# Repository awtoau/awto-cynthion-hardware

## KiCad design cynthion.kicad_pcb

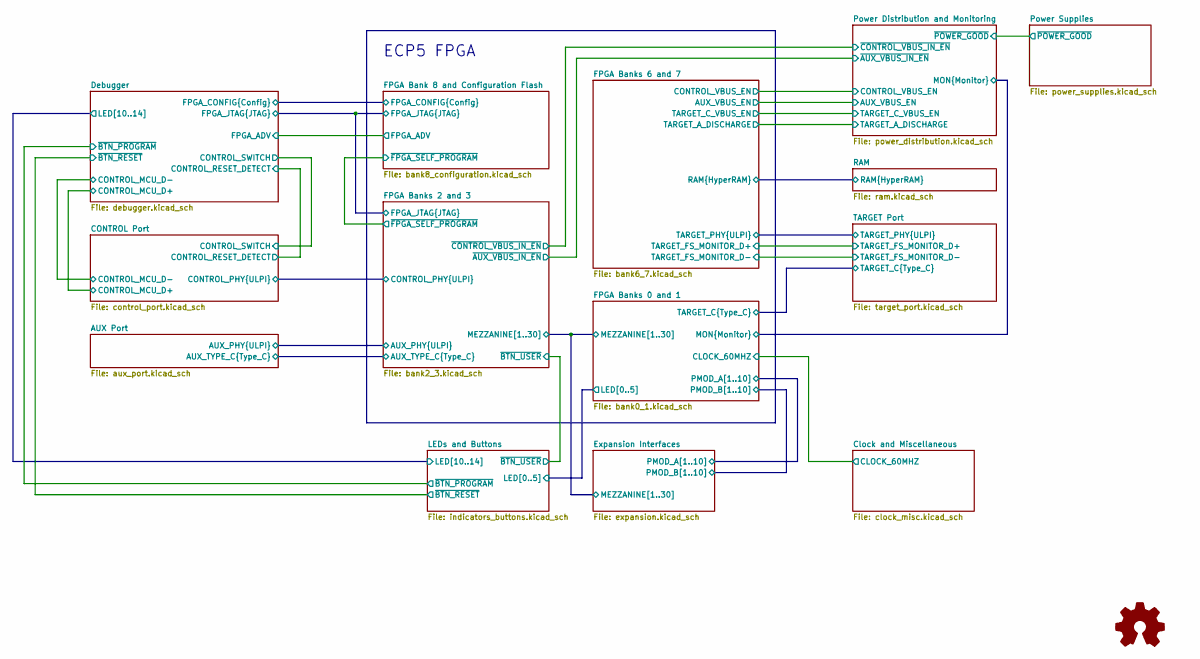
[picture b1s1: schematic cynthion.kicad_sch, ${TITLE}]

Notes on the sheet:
ECP5 FPGA

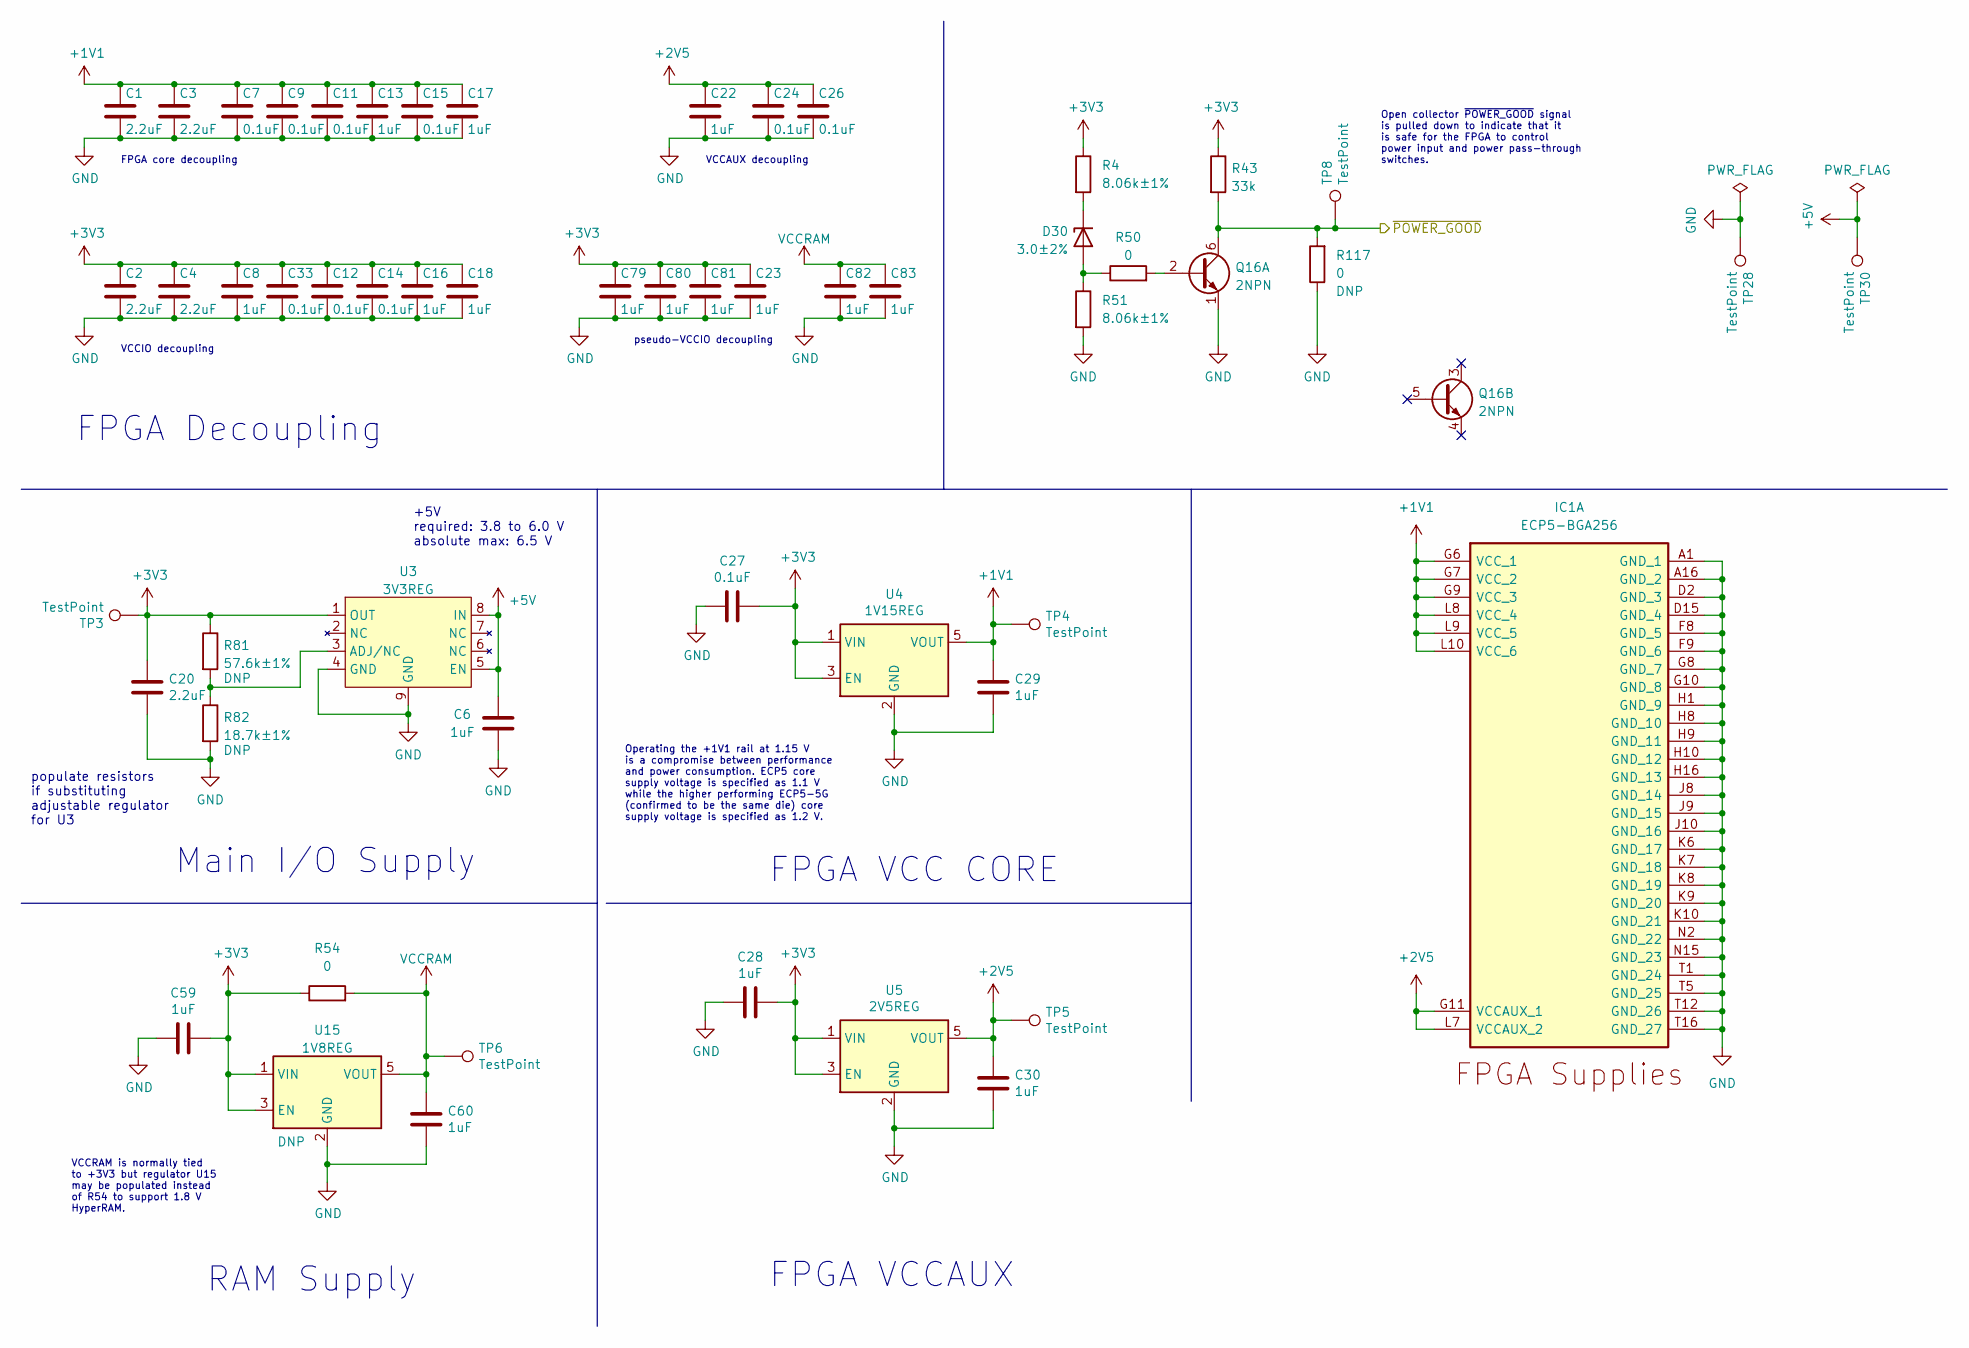
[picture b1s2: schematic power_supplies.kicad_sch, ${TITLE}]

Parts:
C1, C2, C3, C4, C20: 2.2uF; C_0603_1608Metric; Part Number CL10A225KP8NNNC
C6, C8, C13, C16, C17, C18, C22, C23, C28, C29, C30, C59, C60, C79, C80, C81, C82, C83: 1uF; C_0402_1005Metric; Part Number CL05A105MQ5NNNC
C7, C9, C11, C12, C14, C15, C24, C26, C27, C33: 0.1uF; C_0402_1005Metric; Part Number CL05A104KA5NNNC
D30: 3.0±2%; DFN1006-2; Part Number BZX884-B3V0,315
IC1: ECP5-BGA256; lattice_cabga256; Part Number LFE5U-12F-6BG256C
Q16: 2NPN; SOT-363_SC-70-6; Part Number BC847BS
R4, R51: 8.06k±1%; R_0402_1005Metric; Part Number ERJ-2RKF8061X
R43: 33k; R_0402_1005Metric; Part Number ERJ-2GEJ333X
R50, R54, R117: 0; R_0402_1005Metric; Part Number RC0402FR-070RL
R81: 57.6k±1%; R_0402_1005Metric; Part Number RC0402FR-0757K6L
R82: 18.7k±1%; R_0402_1005Metric; Part Number ERJ-2RKF1872X
TP3, TP4, TP5, TP6, TP8, TP28, TP30: TestPoint; TestPoint_Pad_D1.0mm
U3: 3V3REG; DFN-8-1EP_3x3mm_P0.65mm_EP1.55x2.4mm; Part Number AP7361EA-33FGE-7
U4: 1V15REG; SOT-23-5; Part Number TCR2EF115,LM(CT
U5: 2V5REG; SOT-23-5; Part Number MIC5504-2.5YM5-TR
U15: 1V8REG; SOT-23-5; Part Number MIC5504-1.8YM5-TR

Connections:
+1V1: C1.1, C3.1, C7.1, C9.1, C11.1, C13.1, C15.1, C17.1, C29.1, IC1.G6 (VCC_1), IC1.G7 (VCC_2), IC1.G9 (VCC_3), IC1.L8 (VCC_4), IC1.L9 (VCC_5), IC1.L10 (VCC_6), TP4.1 (1_1), U4.5 (VOUT)
+2V5: C22.1, C24.1, C26.1, C30.1, IC1.G11 (VCCAUX_1), IC1.L7 (VCCAUX_2), TP5.1 (1_1), U5.5 (VOUT)
+3V3: C2.1, C4.1, C8.1, C12.1, C14.1, C16.1, C18.1, C20.1, C23.1, C27.1, C28.1, C33.1, C59.1, C79.1, C80.1, C81.1, R4.1, R43.1, R54.1, R81.1, TP3.1 (1_1), U3.1 (OUT), U4.1 (VIN), U4.3 (EN), U5.1 (VIN), U5.3 (EN), U15.1 (VIN), U15.3 (EN); also elsewhere on the board
+5V: C6.1, TP30.1 (1_1), U3.5 (EN), U3.8 (IN); also elsewhere on the board
/Power Distribution and Monitoring/~POWER_GOOD: Q16.6 (C1), R43.2, R117.2, TP8.1 (1_1); also elsewhere on the board
GND: C1.2, C2.2, C3.2, C4.2, C6.2, C7.2, C8.2, C9.2, C11.2, C12.2, C13.2, C14.2, C15.2, C16.2, C17.2, C18.2, C20.2, C22.2, C23.2, C24.2, C26.2, C27.2, C28.2, C29.2, C30.2, C33.2, C59.2, C60.2, C79.2, C80.2, C81.2, C82.2, C83.2, IC1.A1 (GND_1), IC1.A16 (GND_2), IC1.D2 (GND_3), IC1.D15 (GND_4), IC1.F8 (GND_5), IC1.F9 (GND_6), IC1.G8 (GND_7), IC1.G10 (GND_8), IC1.H1 (GND_9), IC1.H8 (GND_10), IC1.H9 (GND_11), IC1.H10 (GND_12), IC1.H16 (GND_13), IC1.J8 (GND_14), IC1.J9 (GND_15), IC1.J10 (GND_16), IC1.K6 (GND_17), IC1.K7 (GND_18), IC1.K8 (GND_19), IC1.K9 (GND_20), IC1.K10 (GND_21), IC1.N2 (GND_22), IC1.N15 (GND_23), IC1.T1 (GND_24), IC1.T5 (GND_25), IC1.T12 (GND_26), IC1.T16 (GND_27), Q16.1 (E1), R51.2, R82.2, R117.1, TP28.1 (1_1), U3.4 (GND), U3.9 (GND), U4.2 (GND), U5.2 (GND), U15.2 (GND); also elsewhere on the board
unnamed: D30.2 (A), R50.1, R51.1
unnamed: D30.1 (K), R4.2
unnamed: Q16.2 (B1), R50.2
unnamed: R81.2, R82.1, U3.3 (ADJ/NC)
VCCRAM: C60.1, C82.1, C83.1, R54.2, TP6.1 (1_1), U15.5 (VOUT); also elsewhere on the board

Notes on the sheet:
VCCIO decoupling
FPGA VCC CORE
FPGA Decoupling
FPGA core decoupling
+5V required: 3.8 to 6.0 V absolute max: 6.5 V
VCCRAM is normally tied to +3V3 but regulator U15 may be populated instead of R54 to support 1.8 V HyperRAM.
Open collector ~{POWER_GOOD} signal is pulled down to indicate that it is safe for the FPGA to control power input and power pass-through switches.
VCCAUX decoupling
FPGA VCCAUX
Main I/O Supply
populate resistors if substituting adjustable regulator for U3
RAM Supply
Operating the +1V1 rail at 1.15 V is a compromise between performance and power consumption. ECP5 core supply voltage is specified as 1.1 V while the higher performing ECP5-5G (confirmed to be the same die) core supply voltage is specified as 1.2 V.
pseudo-VCCIO decoupling

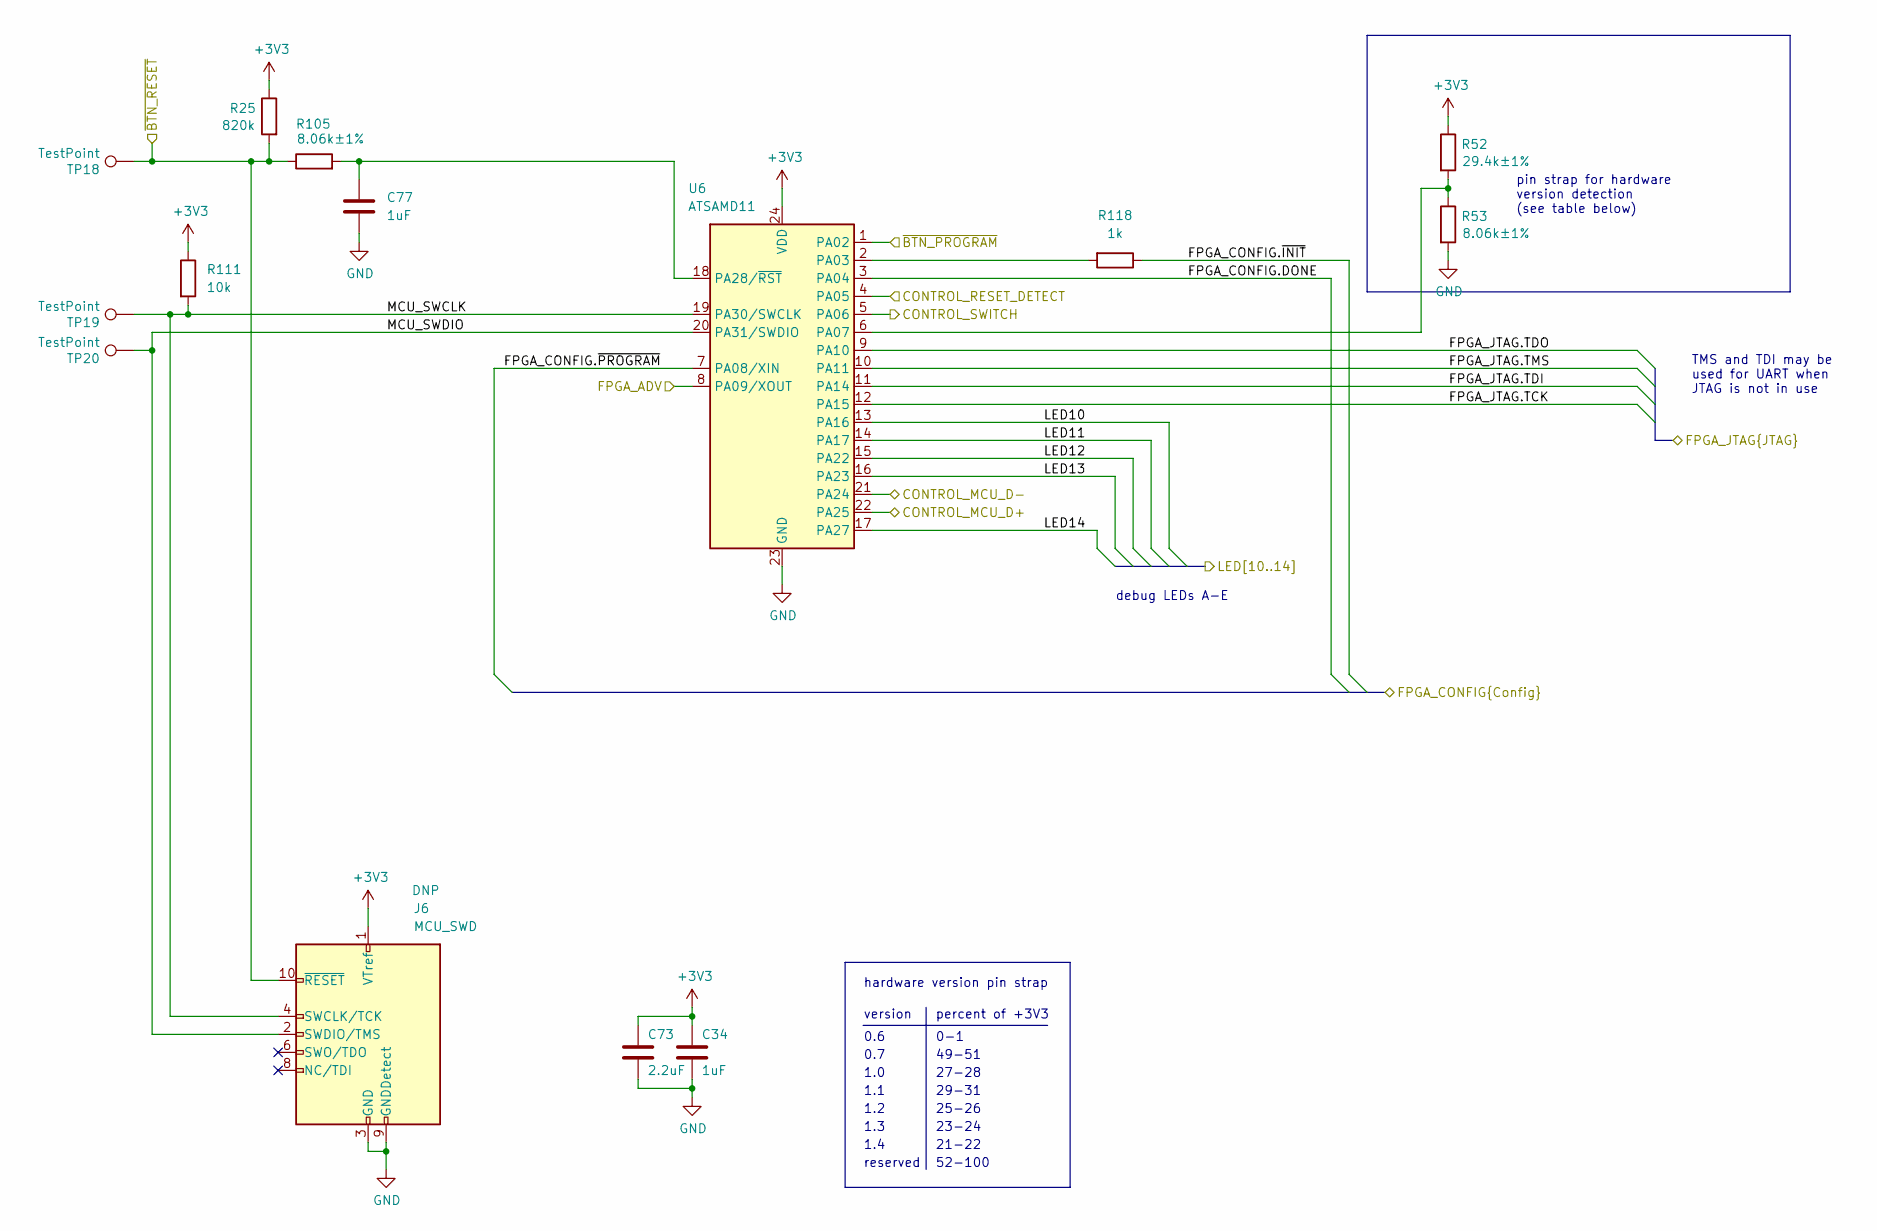
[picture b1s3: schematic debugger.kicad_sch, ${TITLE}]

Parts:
C34, C77: 1uF; C_0402_1005Metric; Part Number CL05A105MQ5NNNC
C73: 2.2uF; C_0603_1608Metric; Part Number CL10A225KP8NNNC
J6: MCU_SWD; SWD_CONNECTOR_LARGE_BOX; Part Number FTSH-105-01-F-D-K
R25: 820k; R_0402_1005Metric; Part Number RC0402JR-07820KL
R52: 29.4k±1%; R_0402_1005Metric; Part Number RC0402FR-0729K4L
R53, R105: 8.06k±1%; R_0402_1005Metric; Part Number ERJ-2RKF8061X
R111: 10k; R_0402_1005Metric; Part Number RC0402JR-0710KL
R118: 1k; R_0402_1005Metric; Part Number RC0402JR-071KL
TP18, TP19, TP20: TestPoint; TestPoint_Pad_D1.0mm
U6: ATSAMD11; QFN-24-1EP_4x4mm_P0.5mm_EP2.6x2.6mm; Part Number ATSAMD11D14A-MUT

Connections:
+3V3: C34.1, C73.1, J6.1 (VTref), R25.1, R52.1, R111.1, U6.24 (VDD); also elsewhere on the board
/CONTROL Port/CONTROL_MCU_D+: U6.22 (PA25); also elsewhere on the board
/CONTROL Port/CONTROL_MCU_D-: U6.21 (PA24); also elsewhere on the board
/CONTROL Port/CONTROL_RESET_DETECT: U6.4 (PA05); also elsewhere on the board
/CONTROL Port/CONTROL_SWITCH: U6.5 (PA06); also elsewhere on the board
/Debugger/FPGA_ADV: U6.8 (PA09/XOUT); also elsewhere on the board
/Debugger/FPGA_CONFIG.DONE: U6.3 (PA04); also elsewhere on the board
/Debugger/FPGA_CONFIG.~INIT: R118.1; also elsewhere on the board
/Debugger/FPGA_CONFIG.~PROGRAM: U6.7 (PA08/XIN); also elsewhere on the board
/Debugger/FPGA_JTAG.TCK: U6.12 (PA15); also elsewhere on the board
/Debugger/FPGA_JTAG.TDI: U6.11 (PA14); also elsewhere on the board
/Debugger/FPGA_JTAG.TDO: U6.9 (PA10); also elsewhere on the board
/Debugger/FPGA_JTAG.TMS: U6.10 (PA11); also elsewhere on the board
/Debugger/LED10: U6.13 (PA16); also elsewhere on the board
/Debugger/LED11: U6.14 (PA17); also elsewhere on the board
/Debugger/LED12: U6.15 (PA22); also elsewhere on the board
/Debugger/LED13: U6.16 (PA23); also elsewhere on the board
/Debugger/LED14: U6.17 (PA27); also elsewhere on the board
/Debugger/MCU_SWCLK: J6.4 (SWCLK/TCK), R111.2, TP19.1 (1_1), U6.19 (PA30/SWCLK)
/Debugger/MCU_SWDIO: J6.2 (SWDIO/TMS), TP20.1 (1_1), U6.20 (PA31/SWDIO)
/Debugger/~BTN_PROGRAM: U6.1 (PA02); also elsewhere on the board
/Debugger/~BTN_RESET: J6.10 (~RESET), R25.2, R105.1, TP18.1 (1_1); also elsewhere on the board
GND: C34.2, C73.2, C77.2, J6.3 (GND), J6.5 (GND), J6.9 (GNDDetect), R53.2, U6.23 (GND); also elsewhere on the board
unnamed: R118.2, U6.2 (PA03)
unnamed: R52.2, R53.1, U6.6 (PA07)
unnamed: C77.1, R105.2, U6.18 (PA28/~RST)

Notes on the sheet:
1.4
debug LEDs A-E
reserved
27-28
52-100
version
25-26
percent of +3V3
TMS and TDI may be used for UART when JTAG is not in use
29-31
0.6
0-1
1.0
23-24
pin strap for hardware version detection (see table below)
49-51
1.2
0.7
1.3
21-22
1.1
hardware version pin strap

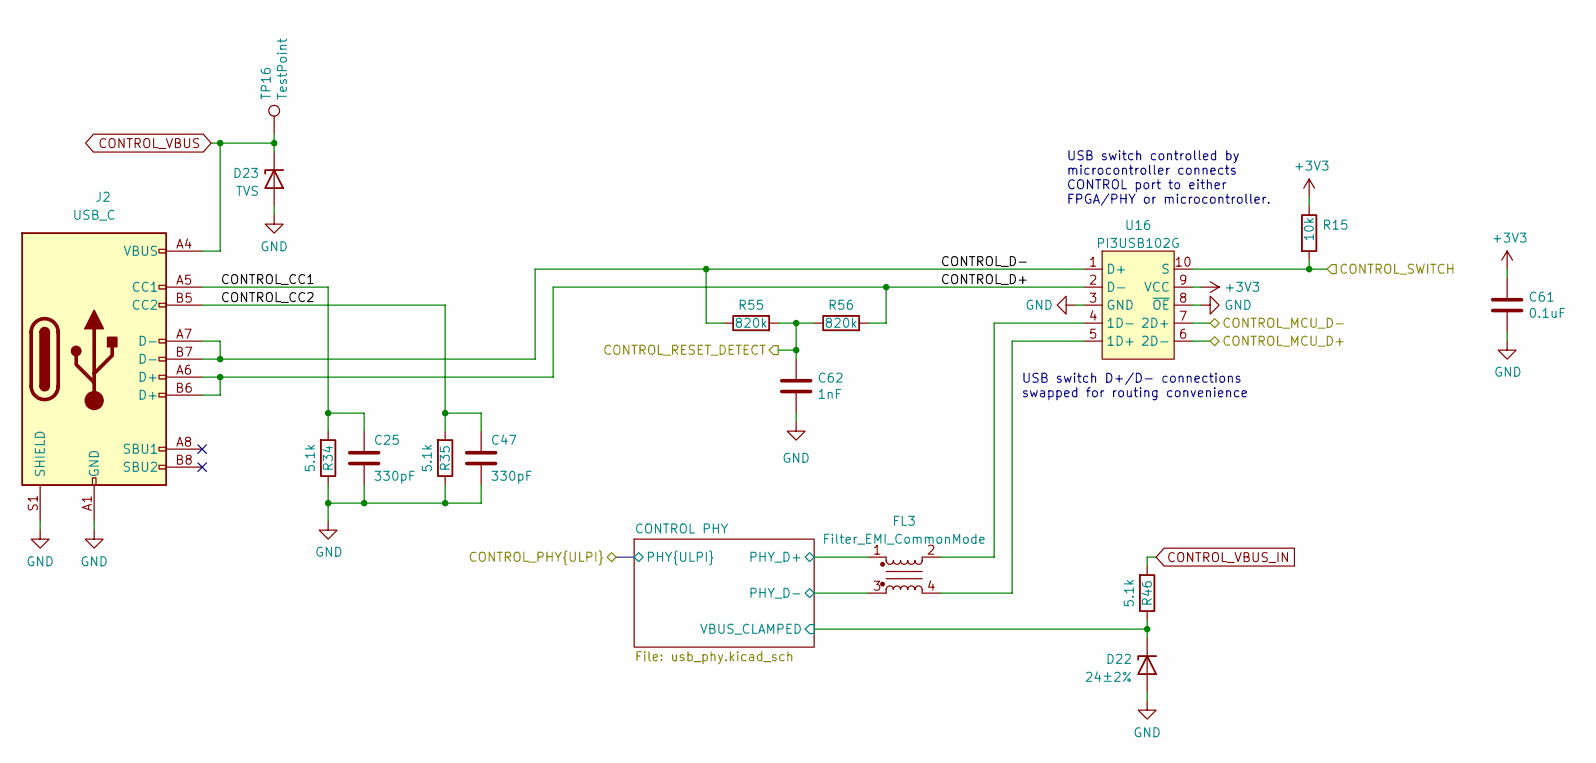
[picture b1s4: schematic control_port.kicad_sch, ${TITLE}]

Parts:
C25, C47: 330pF; C_0402_1005Metric; Part Number CL05C331JB5NNNC
C61: 0.1uF; C_0402_1005Metric; Part Number CL05A104KA5NNNC
C62: 1nF; C_0402_1005Metric; Part Number CL05B102KB5NNNC
D22: 24±2%; DFN1006-2; Part Number BZX884-B24,315
D23: TVS; DFN1006-2; Part Number PESD36VS1UL,315
FL3: Filter_EMI_CommonMode; L_CommonModeChoke_Murata_DLM0NS; Part Number DLM0NSB280HY2D
J2: USB_C; USB_C_Receptacle_HRO_TYPE-C-31-M-12; Part Number USB-TYPE-C-019
R15: 10k; R_0402_1005Metric; Part Number RC0402JR-0710KL
R34, R35, R46: 5.1k; R_0402_1005Metric; Part Number RC0402JR-075K1L
R55, R56: 820k; R_0402_1005Metric; Part Number RC0402JR-07820KL
TP16: TestPoint; TestPoint_Pad_D1.0mm
U16: PI3USB102G; Diodes_10-TQFN_ZL; Part Number PI3USB102GZLEX

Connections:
+3V3: C61.1, R15.1, U16.9 (VCC); also elsewhere on the board
/CONTROL Port/CONTROL PHY/PHY_D+: FL3.1; also elsewhere on the board
/CONTROL Port/CONTROL PHY/PHY_D-: FL3.3; also elsewhere on the board
/CONTROL Port/CONTROL PHY/VBUS_CLAMPED: D22.1 (K), R46.1; also elsewhere on the board
/CONTROL Port/CONTROL_CC1: C25.1, J2.A5 (CC1), R34.2
/CONTROL Port/CONTROL_CC2: C47.1, J2.B5 (CC2), R35.2
/CONTROL Port/CONTROL_D+: J2.A6 (D+), J2.B6 (D+), R56.2, U16.2 (D-)
/CONTROL Port/CONTROL_D-: J2.A7 (D-), J2.B7 (D-), R55.1, U16.1 (D+)
/CONTROL Port/CONTROL_MCU_D+: U16.6 (2D-); also elsewhere on the board
/CONTROL Port/CONTROL_MCU_D-: U16.7 (2D+); also elsewhere on the board
/CONTROL Port/CONTROL_RESET_DETECT: C62.1, R55.2, R56.1; also elsewhere on the board
/CONTROL Port/CONTROL_SWITCH: R15.2, U16.10 (S); also elsewhere on the board
CONTROL_VBUS: D23.1 (K), J2.A4 (VBUS), J2.A9 (VBUS), J2.B4 (VBUS), J2.B9 (VBUS), TP16.1 (1_1); also elsewhere on the board
CONTROL_VBUS_IN: R46.2; also elsewhere on the board
GND: C25.2, C47.2, C61.2, C62.2, D22.2 (A), D23.2 (A), J2.A1 (GND), J2.A12 (GND), J2.B1 (GND), J2.B12 (GND), J2.S1 (SHIELD), R34.1, R35.1, U16.3 (GND), U16.8 (~OE); also elsewhere on the board
unnamed: FL3.4, U16.5 (1D+)
unnamed: FL3.2, U16.4 (1D-)

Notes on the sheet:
USB switch controlled by microcontroller connects CONTROL port to either FPGA/PHY or microcontroller.
USB switch D+/D- connections swapped for routing convenience

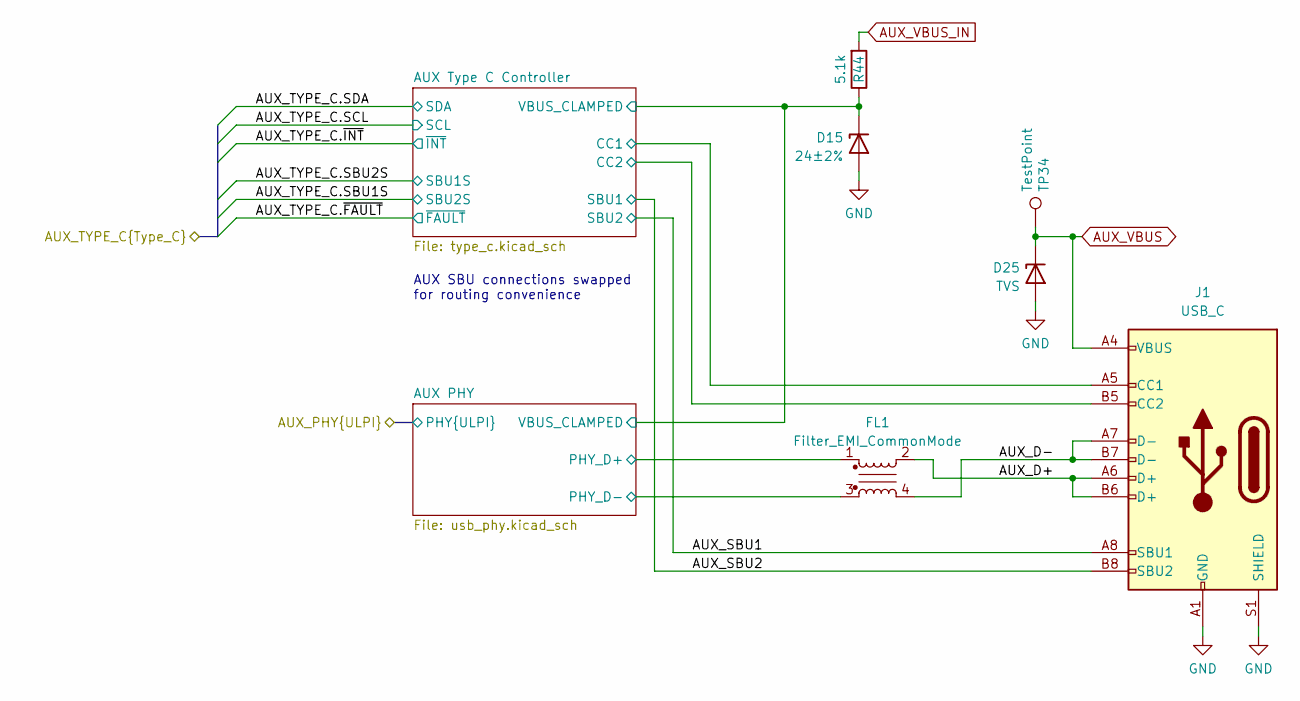
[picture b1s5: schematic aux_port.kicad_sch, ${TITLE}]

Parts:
D15: 24±2%; DFN1006-2; Part Number BZX884-B24,315
D25: TVS; DFN1006-2; Part Number PESD36VS1UL,315
FL1: Filter_EMI_CommonMode; L_CommonModeChoke_Murata_DLM0NS; Part Number DLM0NSB280HY2D
J1: USB_C; USB_C_Receptacle_HRO_TYPE-C-31-M-12; Part Number USB-TYPE-C-019
R44: 5.1k; R_0402_1005Metric; Part Number RC0402JR-075K1L
TP34: TestPoint; TestPoint_Pad_D1.0mm

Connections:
/AUX Port/AUX PHY/PHY_D+: FL1.1; also elsewhere on the board
/AUX Port/AUX PHY/PHY_D-: FL1.3; also elsewhere on the board
/AUX Port/AUX PHY/VBUS_CLAMPED: D15.1 (K), R44.1; also elsewhere on the board
/AUX Port/AUX Type C Controller/CC1: J1.A5 (CC1); also elsewhere on the board
/AUX Port/AUX Type C Controller/CC2: J1.B5 (CC2); also elsewhere on the board
/AUX Port/AUX_D+: FL1.2, J1.A6 (D+), J1.B6 (D+)
/AUX Port/AUX_D-: FL1.4, J1.A7 (D-), J1.B7 (D-)
/AUX Port/AUX_SBU1: J1.A8 (SBU1); also elsewhere on the board
/AUX Port/AUX_SBU2: J1.B8 (SBU2); also elsewhere on the board
AUX_VBUS: D25.1 (K), J1.A4 (VBUS), J1.A9 (VBUS), J1.B4 (VBUS), J1.B9 (VBUS), TP34.1 (1_1); also elsewhere on the board
AUX_VBUS_IN: R44.2; also elsewhere on the board
GND: D15.2 (A), D25.2 (A), J1.A1 (GND), J1.A12 (GND), J1.B1 (GND), J1.B12 (GND), J1.S1 (SHIELD); also elsewhere on the board

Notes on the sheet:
AUX SBU connections swapped for routing convenience

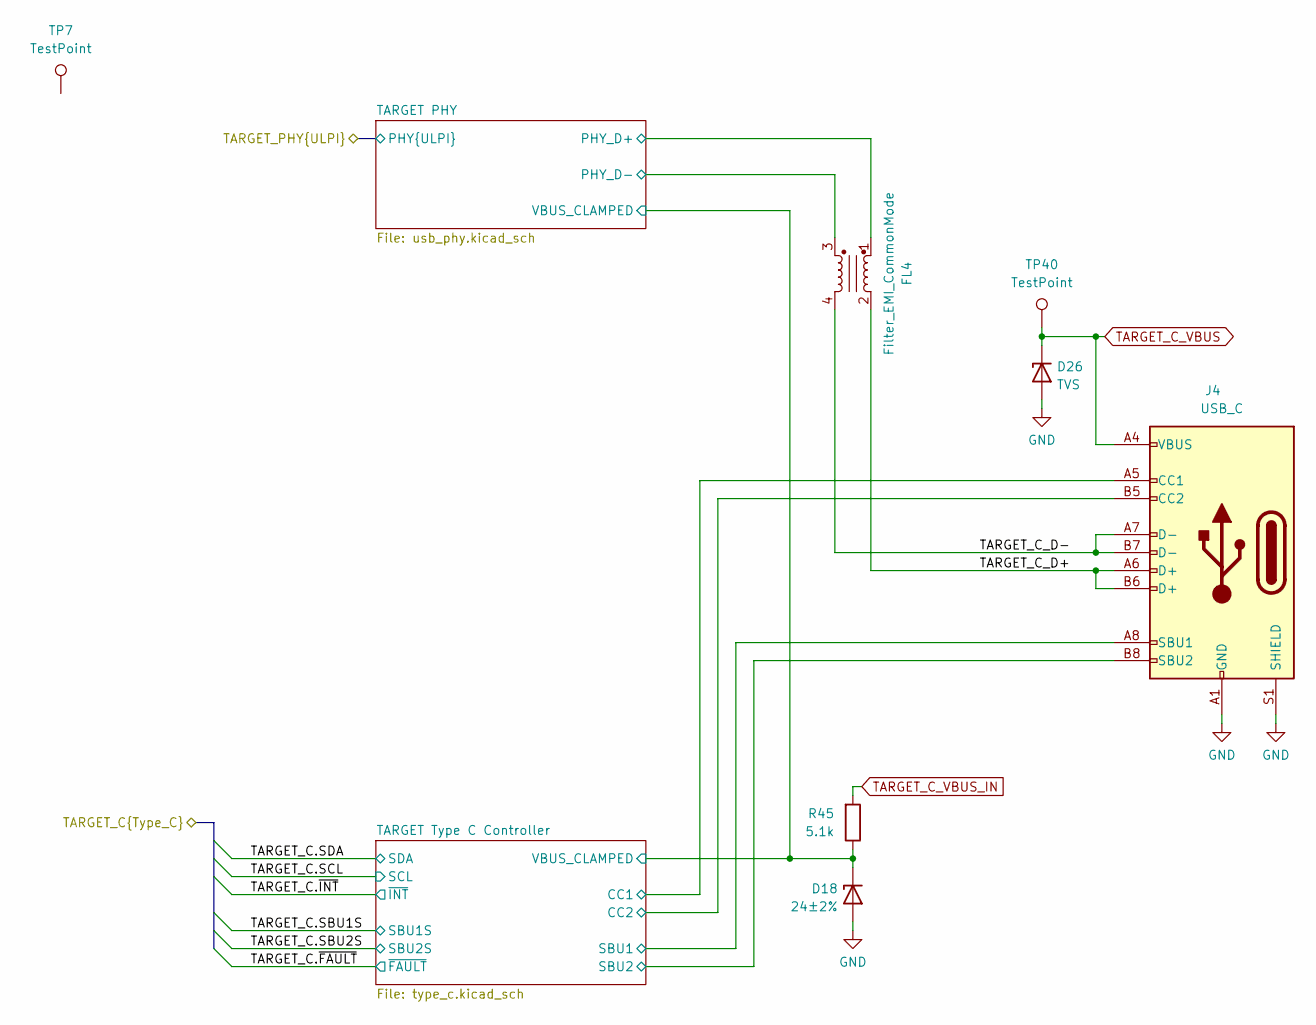
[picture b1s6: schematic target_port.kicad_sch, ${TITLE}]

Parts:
D18: 24±2%; DFN1006-2; Part Number BZX884-B24,315
D26: TVS; DFN1006-2; Part Number PESD36VS1UL,315
FL4: Filter_EMI_CommonMode; L_CommonModeChoke_Murata_DLM0NS; Part Number DLM0NSB280HY2D
J4: USB_C; USB_C_Receptacle_HRO_TYPE-C-31-M-12; Part Number USB-TYPE-C-019
R45: 5.1k; R_0402_1005Metric; Part Number RC0402JR-075K1L
TP7, TP40: TestPoint; TestPoint_Pad_D1.0mm

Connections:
/TARGET Port/TARGET PHY/PHY_D+: FL4.1; also elsewhere on the board
/TARGET Port/TARGET PHY/PHY_D-: FL4.3; also elsewhere on the board
/TARGET Port/TARGET PHY/VBUS_CLAMPED: D18.1 (K), R45.1; also elsewhere on the board
/TARGET Port/TARGET Type C Controller/CC1: J4.A5 (CC1); also elsewhere on the board
/TARGET Port/TARGET Type C Controller/CC2: J4.B5 (CC2); also elsewhere on the board
/TARGET Port/TARGET Type C Controller/SBU1: J4.A8 (SBU1); also elsewhere on the board
/TARGET Port/TARGET Type C Controller/SBU2: J4.B8 (SBU2); also elsewhere on the board
/TARGET Port/TARGET_C_D+: FL4.2, J4.A6 (D+), J4.B6 (D+)
/TARGET Port/TARGET_C_D-: FL4.4, J4.A7 (D-), J4.B7 (D-)
GND: D18.2 (A), D26.2 (A), J4.A1 (GND), J4.A12 (GND), J4.B1 (GND), J4.B12 (GND), J4.S1 (SHIELD); also elsewhere on the board
TARGET_C_VBUS: D26.1 (K), J4.A4 (VBUS), J4.A9 (VBUS), J4.B4 (VBUS), J4.B9 (VBUS), TP40.1 (1_1); also elsewhere on the board
TARGET_C_VBUS_IN: R45.2; also elsewhere on the board

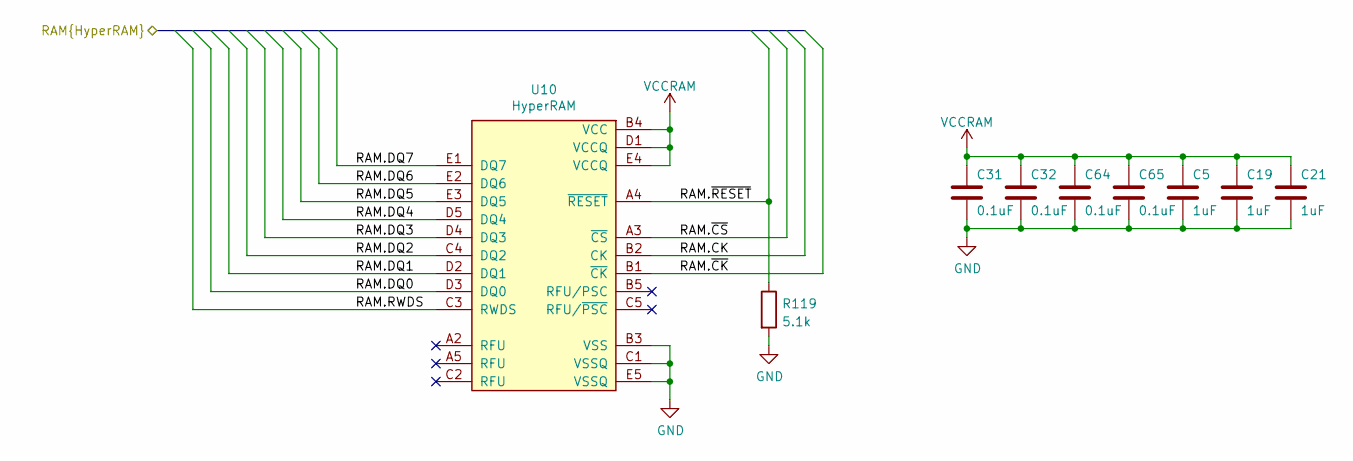
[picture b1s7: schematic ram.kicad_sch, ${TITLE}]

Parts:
C5, C19, C21: 1uF; C_0402_1005Metric; Part Number CL05A105MQ5NNNC
C31, C32, C64, C65: 0.1uF; C_0402_1005Metric; Part Number CL05A104KA5NNNC
R119: 5.1k; R_0402_1005Metric; Part Number RC0402JR-075K1L
U10: HyperRAM; BGA-24_5x5_6.0x8.0mm; Part Number W956A8MBYA6I

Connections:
/FPGA Banks 6 and 7/RAM.CK: U10.B2 (CK); also elsewhere on the board
/FPGA Banks 6 and 7/RAM.DQ0: U10.D3 (DQ0); also elsewhere on the board
/FPGA Banks 6 and 7/RAM.DQ1: U10.D2 (DQ1); also elsewhere on the board
/FPGA Banks 6 and 7/RAM.DQ2: U10.C4 (DQ2); also elsewhere on the board
/FPGA Banks 6 and 7/RAM.DQ3: U10.D4 (DQ3); also elsewhere on the board
/FPGA Banks 6 and 7/RAM.DQ4: U10.D5 (DQ4); also elsewhere on the board
/FPGA Banks 6 and 7/RAM.DQ5: U10.E3 (DQ5); also elsewhere on the board
/FPGA Banks 6 and 7/RAM.DQ6: U10.E2 (DQ6); also elsewhere on the board
/FPGA Banks 6 and 7/RAM.DQ7: U10.E1 (DQ7); also elsewhere on the board
/FPGA Banks 6 and 7/RAM.RWDS: U10.C3 (RWDS); also elsewhere on the board
/FPGA Banks 6 and 7/RAM.~CK: U10.B1 (~CK); also elsewhere on the board
/FPGA Banks 6 and 7/RAM.~CS: U10.A3 (~CS); also elsewhere on the board
/FPGA Banks 6 and 7/RAM.~RESET: R119.1, U10.A4 (~RESET); also elsewhere on the board
GND: C5.2, C19.2, C21.2, C31.2, C32.2, C64.2, C65.2, R119.2, U10.B3 (VSS), U10.C1 (VSSQ), U10.E5 (VSSQ); also elsewhere on the board
VCCRAM: C5.1, C19.1, C21.1, C31.1, C32.1, C64.1, C65.1, U10.B4 (VCC), U10.D1 (VCCQ), U10.E4 (VCCQ); also elsewhere on the board

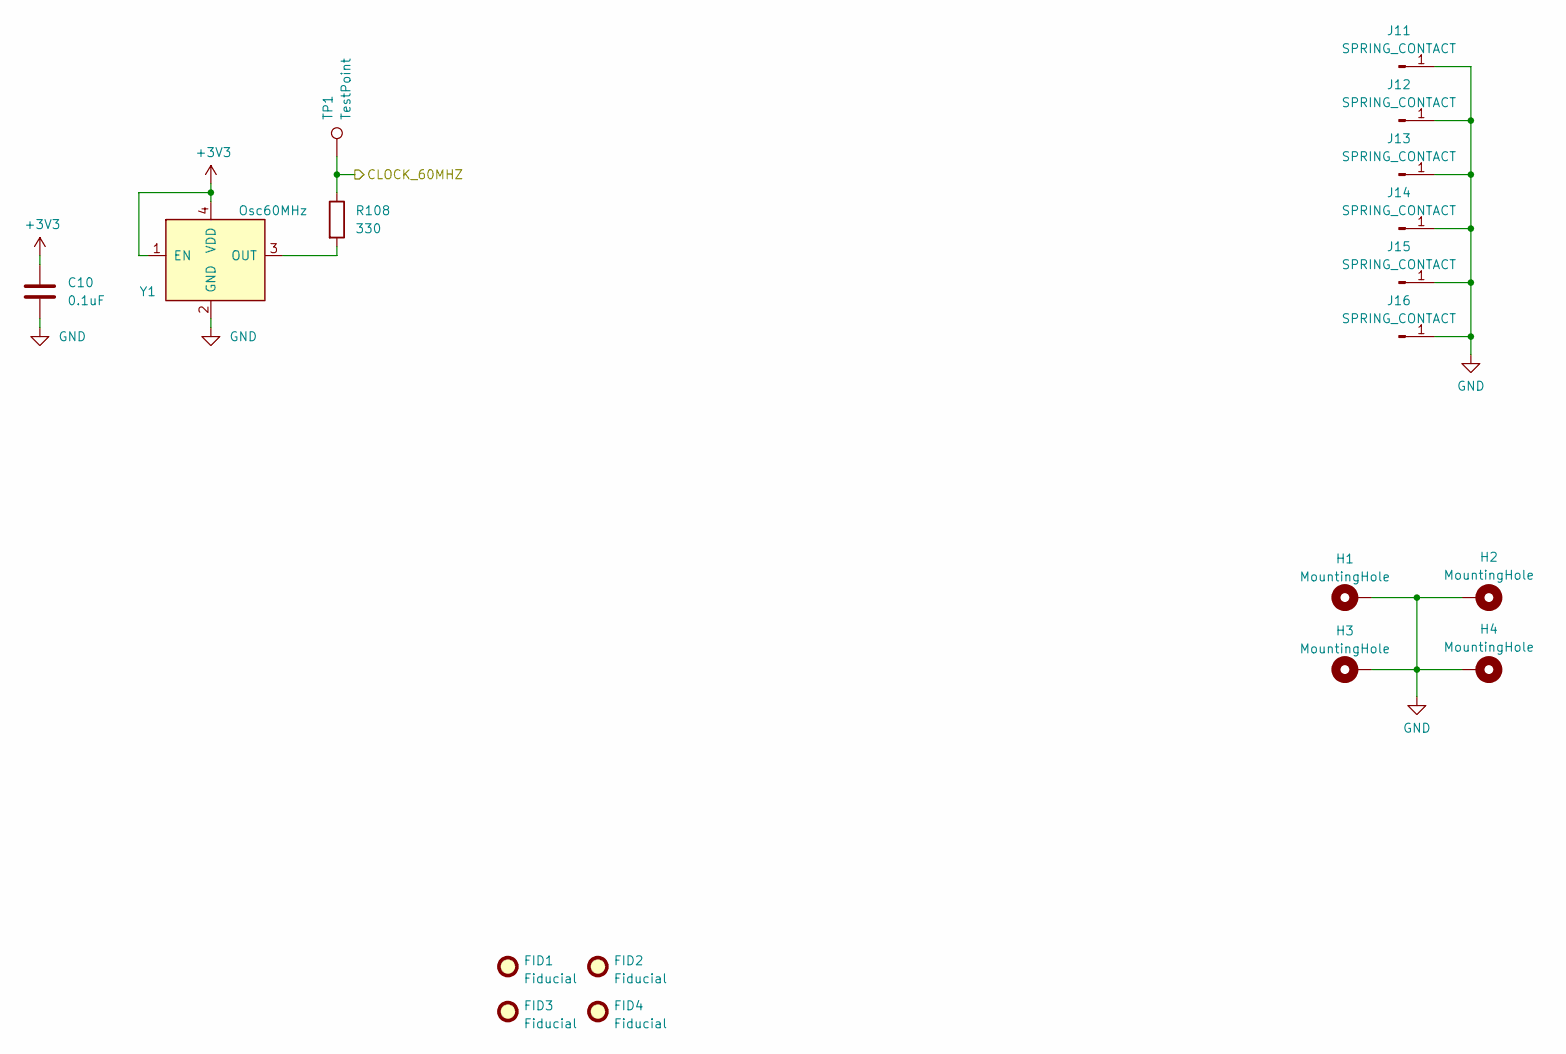
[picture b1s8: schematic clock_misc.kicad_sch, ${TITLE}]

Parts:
C10: 0.1uF; C_0402_1005Metric; Part Number CL05A104KA5NNNC
FID1, FID2, FID3, FID4: Fiducial; Fiducial_0.5mm_Mask1mm
H1, H2, H3, H4: MountingHole; MountingHole_2.2mm_M2_Pad_Via
J11, J12, J13, J14, J15, J16: SPRING_CONTACT; BW0033AG-L3.4W0.9H1.8; Part Number BW0033AG-L3.4W0.9H1.8
R108: 330; R_0402_1005Metric; Part Number RC0402FR-13330RL
TP1: TestPoint; TestPoint_Pad_D1.0mm
Y1: Osc60MHz; Crystal_SMD_3225-4Pin_3.2x2.5mm; Part Number SIT1602BC-23-33E-60.000000E

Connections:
+3V3: C10.1, Y1.1 (EN), Y1.4 (VDD); also elsewhere on the board
/Clock and Miscellaneous/CLOCK_60MHZ: R108.1, TP1.1 (1_1); also elsewhere on the board
GND: C10.2, H1.1 (1_1), H2.1 (1_1), H3.1 (1_1), H4.1 (1_1), J11.1 (Pin_1_1), J12.1 (Pin_1_1), J13.1 (Pin_1_1), J14.1 (Pin_1_1), J15.1 (Pin_1_1), J16.1 (Pin_1_1), Y1.2 (GND); also elsewhere on the board
unnamed: R108.2, Y1.3 (OUT)

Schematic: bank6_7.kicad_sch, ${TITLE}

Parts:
IC1: ECP5-BGA256; lattice_cabga256; Part Number LFE5U-12F-6BG256C

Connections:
+3V3: IC1.J6 (VCCIO6_1), IC1.J7 (VCCIO6_2), IC1.L4 (PL29C), IC1.M4 (PL35C), IC1.M5 (PL44C), IC1.M6 (PL47A), IC1.N5 (PL44D), IC1.P4 (PL41A), IC1.R5 (PL44A); also elsewhere on the board
/FPGA Banks 6 and 7/AUX_VBUS_EN: IC1.L2 (PL26B); also elsewhere on the board
/FPGA Banks 6 and 7/CONTROL_VBUS_EN: IC1.L1 (PL26A); also elsewhere on the board
/FPGA Banks 6 and 7/RAM.CK: IC1.C3 (PL2C); also elsewhere on the board
/FPGA Banks 6 and 7/RAM.DQ0: IC1.F2 (PL11C); also elsewhere on the board
/FPGA Banks 6 and 7/RAM.DQ1: IC1.B1 (PL2A); also elsewhere on the board
/FPGA Banks 6 and 7/RAM.DQ2: IC1.C2 (PL5B); also elsewhere on the board
/FPGA Banks 6 and 7/RAM.DQ3: IC1.E1 (PL11D); also elsewhere on the board
/FPGA Banks 6 and 7/RAM.DQ4: IC1.E3 (PL5C); also elsewhere on the board
/FPGA Banks 6 and 7/RAM.DQ5: IC1.E2 (PL8B); also elsewhere on the board
/FPGA Banks 6 and 7/RAM.DQ6: IC1.F3 (PL5D); also elsewhere on the board
/FPGA Banks 6 and 7/RAM.DQ7: IC1.G4 (PL11B); also elsewhere on the board
/FPGA Banks 6 and 7/RAM.RWDS: IC1.D1 (PL8A); also elsewhere on the board
/FPGA Banks 6 and 7/RAM.~CK: IC1.D3 (PL2D); also elsewhere on the board
/FPGA Banks 6 and 7/RAM.~CS: IC1.B2 (PL2B); also elsewhere on the board
/FPGA Banks 6 and 7/RAM.~RESET: IC1.C1 (PL5A); also elsewhere on the board
/FPGA Banks 6 and 7/TARGET_A_DISCHARGE: IC1.K4 (PL29A); also elsewhere on the board
/FPGA Banks 6 and 7/TARGET_C_VBUS_EN: IC1.K5 (PL29B); also elsewhere on the board
/FPGA Banks 6 and 7/TARGET_FS_MONITOR_D+: IC1.N4 (PL38A)
/FPGA Banks 6 and 7/TARGET_FS_MONITOR_D-: IC1.P3 (PL38B)
/FPGA Banks 6 and 7/TARGET_PHY.CLK: IC1.T4 (PL44B); also elsewhere on the board
/FPGA Banks 6 and 7/TARGET_PHY.DATA0: IC1.R2 (PL38C); also elsewhere on the board
/FPGA Banks 6 and 7/TARGET_PHY.DATA1: IC1.R1 (PL35B); also elsewhere on the board
/FPGA Banks 6 and 7/TARGET_PHY.DATA2: IC1.P2 (PL32B); also elsewhere on the board
/FPGA Banks 6 and 7/TARGET_PHY.DATA3: IC1.P1 (PL35A); also elsewhere on the board
/FPGA Banks 6 and 7/TARGET_PHY.DATA4: IC1.N3 (PL35D); also elsewhere on the board
/FPGA Banks 6 and 7/TARGET_PHY.DATA5: IC1.N1 (PL32A); also elsewhere on the board
/FPGA Banks 6 and 7/TARGET_PHY.DATA6: IC1.M2 (PL26D); also elsewhere on the board
/FPGA Banks 6 and 7/TARGET_PHY.DATA7: IC1.M1 (PL26C); also elsewhere on the board
/FPGA Banks 6 and 7/TARGET_PHY.DIR: IC1.R3 (PL41B); also elsewhere on the board
/FPGA Banks 6 and 7/TARGET_PHY.NXT: IC1.T2 (PL38D); also elsewhere on the board
/FPGA Banks 6 and 7/TARGET_PHY.STP: IC1.T3 (PL41D); also elsewhere on the board
/FPGA Banks 6 and 7/TARGET_PHY.~RESET: IC1.R4 (PL41C); also elsewhere on the board
GND: IC1.F4 (PL8C), IC1.G2 (PL14B), IC1.G3 (PL14C), IC1.H2 (PL20B), IC1.H3 (PL14D), IC1.L3 (PL32C), IC1.L5 (PL29D), IC1.M3 (PL32D), IC1.N6 (PL47B), IC1.P5 (PL47D), IC1.P6 (PL47C); also elsewhere on the board
VCCRAM: IC1.F5 (PL8D), IC1.G5 (PL11A), IC1.H4 (PL17B), IC1.H5 (PL17A), IC1.H6 (VCCIO7_1), IC1.H7 (VCCIO7_2), IC1.J1 (PL23A), IC1.J2 (PL23B), IC1.J3 (PL20C), IC1.J4 (PL17C), IC1.J5 (PL17D); also elsewhere on the board

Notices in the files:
parts and their libraries:
COPYRIGHT: Copyright 2019-2024 Great Scott Gadgets
LICENSE: Licensed under the CERN-OHL-P v2
